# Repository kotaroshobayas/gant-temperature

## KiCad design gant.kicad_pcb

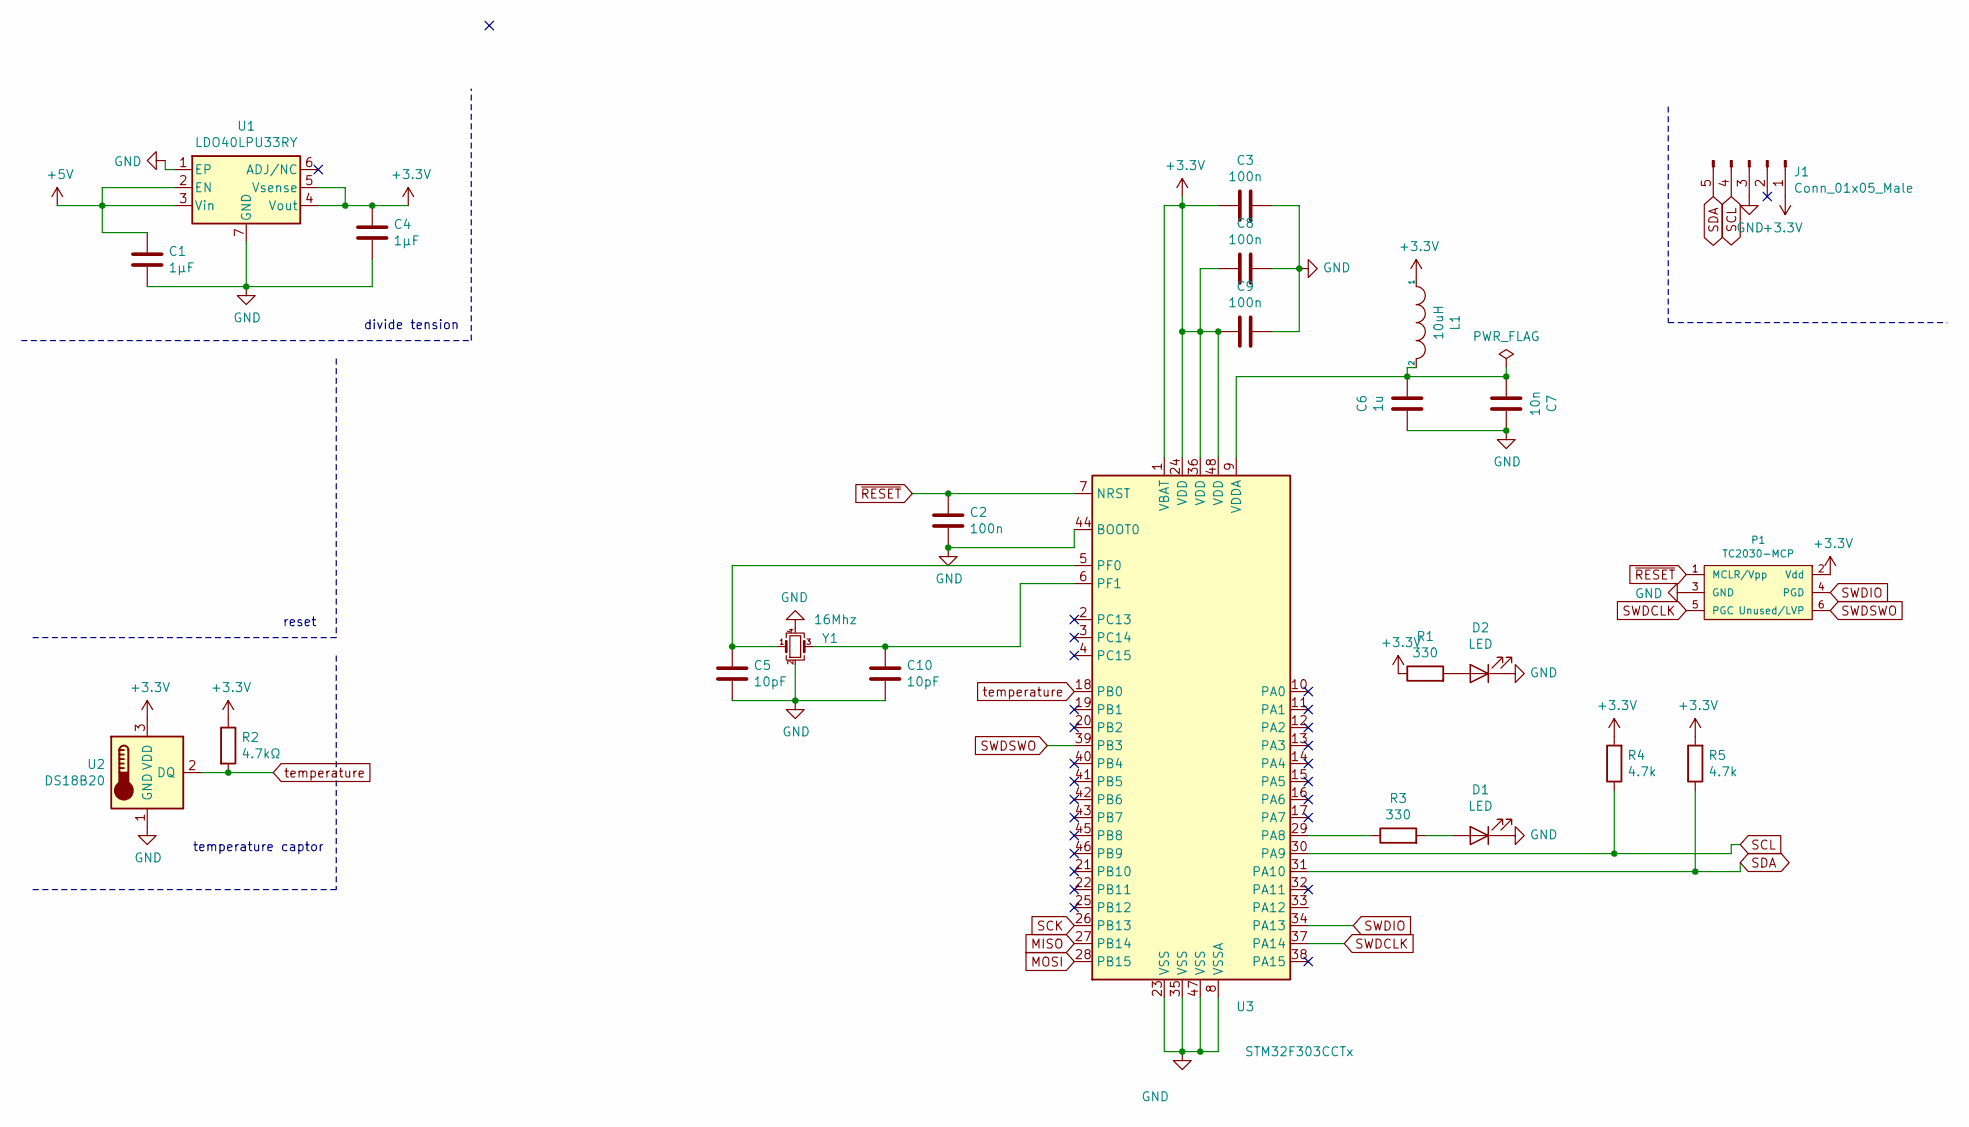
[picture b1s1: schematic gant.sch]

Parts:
C1, C4: 1μF; C_0603_1608Metric
C2, C3, C8, C9: 100n; C_0603_1608Metric
C5, C10: 10pF; C_0603_1608Metric
C6: 1u; C_0603_1608Metric
C7: 10n; C_0603_1608Metric
D1, D2: LED; LED_0603_1608Metric
J1: Conn_01x05_Male; PinHeader_1x05_P2.54mm_Vertical
L1: 10uH; L_0603_1608Metric
P1: TC2030-MCP; TC2030-NL_SMALL
R1, R3: 330; R_0603_1608Metric
R2: 4.7kΩ; R_0603_1608Metric
R4, R5: 4.7k; R_0603_1608Metric
U1: LDO40LPU33RY; DFN-6-1EP_3x3mm_P0.95mm_EP1.7x2.6mm
U2: DS18B20; TO-92_Inline
U3: STM32F303CCTx; LQFP-48_7x7mm_P0.5mm
Y1: 16Mhz; Crystal_SMD_SeikoEpson_FA238-4Pin_3.2x2.5mm

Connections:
+3V3: C3.2, C4.1, C8.2, C9.2, J1.1, L1.1, P1.2 (Vdd), R1.1, R2.1, R4.2, R5.2, U1.4 (Vout), U1.5 (Vsense), U2.3 (VDD), U3.1 (VBAT), U3.24 (VDD), U3.36 (VDD), U3.48 (VDD)
+5V: C1.1, U1.2 (EN), U1.3 (Vin)
GND: C1.2, C2.2, C3.1, C4.2, C5.1, C6.1, C7.1, C8.1, C9.1, C10.1, D1.1 (K), D2.1 (K), J1.3, P1.3 (GND), U1.1 (EP), U1.7 (GND), U2.1 (GND), U3.8 (VSSA), U3.23 (VSS), U3.35 (VSS), U3.44 (BOOT0), U3.47 (VSS), Y1.2, Y1.4
MISO: U3.27 (PB14)
MOSI: U3.28 (PB15)
unnamed: C5.2, U3.5 (PF0), Y1.1
unnamed: C6.2, C7.2, L1.2, U3.9 (VDDA)
unnamed: C10.2, U3.6 (PF1), Y1.3
unnamed: D1.2 (A), R3.2
unnamed: D2.2 (A), R1.2
unnamed: R3.1, U3.29 (PA8)
SCK: U3.26 (PB13)
SCL: J1.4, R4.1, U3.30 (PA9)
SDA: J1.5, R5.1, U3.31 (PA10)
SWDCLK: P1.5 (PGC), U3.37 (PA14)
SWDIO: P1.4 (PGD), U3.34 (PA13)
SWDSWO: P1.6 (Unused/LVP), U3.39 (PB3)
temperature: R2.2, U2.2 (DQ), U3.18 (PB0)
~RESET: C2.1, P1.1 (MCLR/Vpp), U3.7 (NRST)

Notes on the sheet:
divide tension
temperature captor
reset

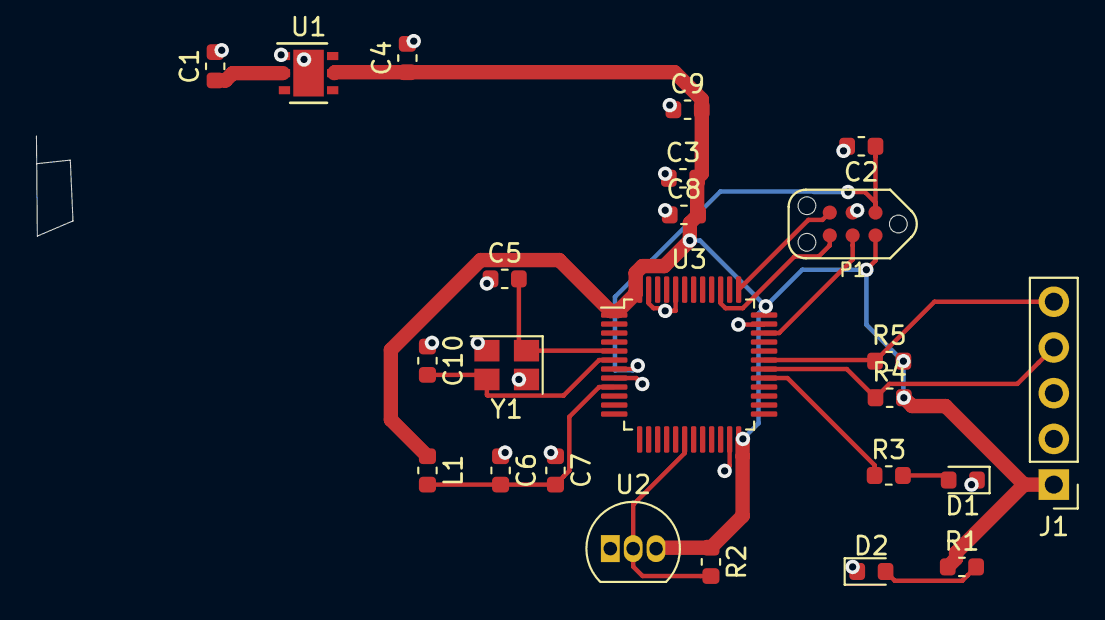
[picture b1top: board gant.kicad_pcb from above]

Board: 2 copper layers, 24 parts (0 on the bottom side), 16 nets.

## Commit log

2019-11-20 initialisation
2019-11-20 test
